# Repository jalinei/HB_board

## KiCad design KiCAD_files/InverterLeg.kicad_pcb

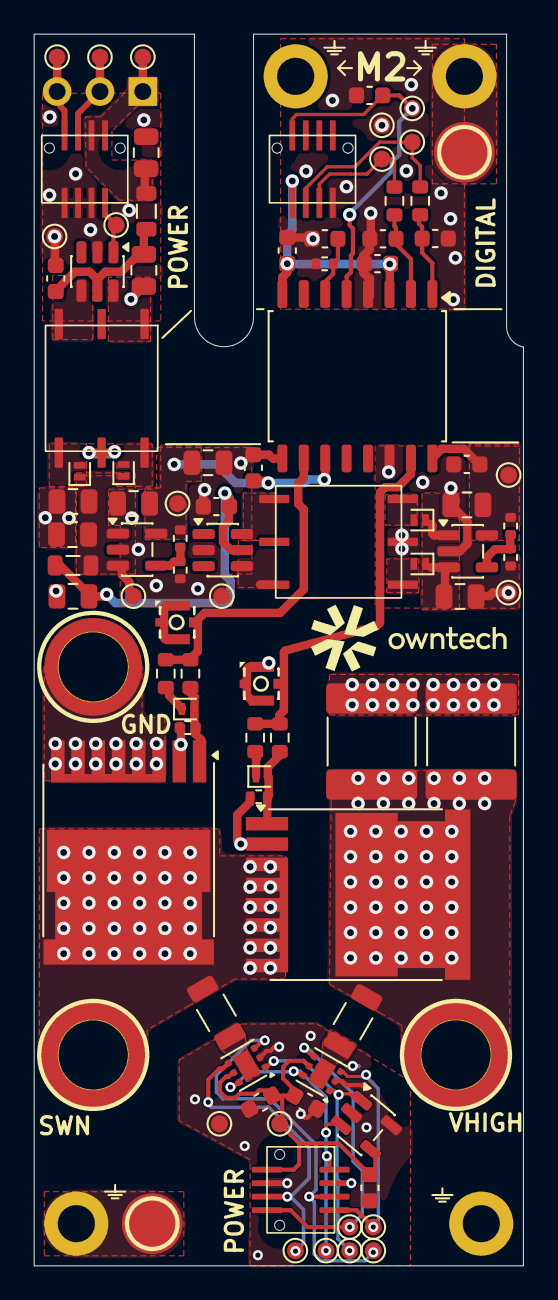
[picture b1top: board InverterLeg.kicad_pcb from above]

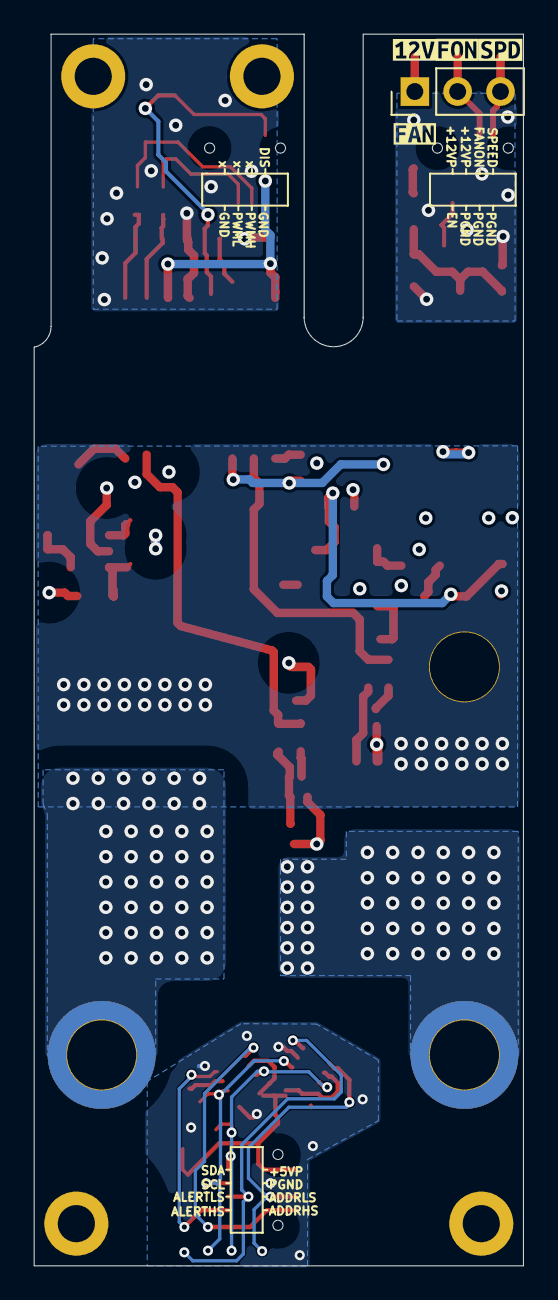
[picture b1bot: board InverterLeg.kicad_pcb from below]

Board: 4 copper layers, 29.0 x 73.0 mm, 100 parts (5 on the bottom side), 52 nets.

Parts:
C602, C605, C612, C614, C713, C733, C751, C754, C755: 100nF; C_0603_1608Metric
C604, C703: 20pF; C_0603_1608Metric
C607, C608: 1nF; C_0603_1608Metric
C616, C709, C711, C717, C718, C719, C731, C732, C734: 10uF; C_0805_2012Metric
C624, C626: 3.3uF; C_2220_5750Metric
D601, D602, D703, D704, D709, D710: PMEG4010ESBYL; D_SOD-882
H801, H802, H803, H804: MountingHole_Pad; MountingHole_2.2mm_M2_DIN965_Pad
J801, J802: AIPEX-4; IPEX-SMD_4P-L1.7-W1.7-LS2.0-L-4
J803, J806: 2LC000-739; CONN-TH_2LC000-739
J804: Conn_01x03_Socket; PinHeader_1x03_P2.54mm_Vertical
J811, J814, J817: SMTSO3050CTJ; SMD-1_BD5.5-D4.0_H5
J825, J827, J831: HC-PBB08-2-08-M-H1.0-G1-R-P-04; HC-PBB02-2-08-Male
L703, L706: 10uH; L_0805_2012Metric
Q801, Q802: AGM15T05LL; Infineon_PG-HSOF-8-2
R601, R602, R603, R604: 1R; R_0603_1608Metric
R605, R606: 51R; R_0603_1608Metric
R607, R608, R611, R613: 10k; R_0402_1005Metric
R609: 20k; R_0402_1005Metric
R610, R612: 158k; R_0402_1005Metric
T801, T802: TE1212-1W6ENT; 12126CNT
TJ801, TJ804: THJP1206AST1; THJP_1206_3216Metric
TP801, TP802, TP803, TP804, TP805, TP806, TP807, TP808, TP809, TP810, TP811, TP812, TP813, TP814, TP815, TP816, TP817, TP818, TP819, TP820, TP821, TP822: TestPoint_Pad_D1.0mm_small_courtyard
U603: UCC21520DWR; SOIC-16W_7.5x10.3mm_P1.27mm
U704, U707: VPS8701B; SOT-23-6
U801, U802: SY6345AAC; TSOT-23-5
U803: 24C02S(XBLW); SOT-23-5
U811, U815: T117B; WSON-6-1EP_2x2mm_P0.65mm_EP1x1.6mm
kibuzzard-6A8EFC0A: G***; kibuzzard-6A8EFC0A
kibuzzard-6A8EFC24: G***; kibuzzard-6A8EFC24
kibuzzard-6A9553CF: G***; kibuzzard-6A9553CF
kibuzzard-6AA2AEDD: G***; kibuzzard-6AA2AEDD

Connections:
+5V_DGND: C602.1, C605.1, J831.5, U603.3 (VCCI), U603.8 (VCCI)
+5V_PGND: C751.1, C754.1, C755.2, J827.1, TP820.1 (1_1), U803.4 (VCC), U811.5 (V+), U815.5 (V+)
+12V_PGND: C709.1, J804.1, J825.1, J825.2, L703.1, TP807.1 (1_1)
/12V_{HSRAW}: C734.1, D709.1 (K), D710.1 (K), U801.1 (VIN), U801.3 (~SHDN)
/12V_{HS}: C612.1, C719.1, R610.2, TP810.1 (1_1), U603.16 (VDDA), U801.5 (VOUT)
/12V_{LSRAW}: C717.1, C731.1, D703.1 (K), D704.1 (K), L706.1, TP814.1 (1_1), U802.1 (VIN), U802.3 (~SHDN)
/12V_{LS}: C614.1, C616.1, C718.1, R612.2, TP812.1 (1_1), U603.11 (VDDB), U802.5 (VOUT)
/ADDR_HS: J827.4, TP822.1 (1_1), U815.4 (ADD0)
/ADDR_LS: J827.3, TP821.1 (1_1), U811.4 (ADD0)
/ALERT_HS: J827.5, TP818.1 (1_1), U815.3 (ALERT)
/ALERT_LS: J827.6, TP817.1 (1_1), U811.3 (ALERT)
/DIS: C608.1, J831.4, TP803.1 (1_1), U603.5 (DIS)
/EN: J825.8, TP805.1 (1_1), U704.1 (EN)
/FAN_{ON}: J804.2, J825.3, TP808.1 (1_1)
/GND_{LS}: C624.2, C626.2, J814.1 (Pin_1_1), Q801.3 (S)
/K_{GNDLS}: C614.2, C616.2, C717.2, C718.2, C731.2, C732.2, C733.2, J802.2 (Ext), J802.3 (Ext), J802.4 (Ext), Q801.2 (DS), R608.1, R613.1, T802.5, TP813.1 (1_1), U603.9 (VSSB), U707.2 (GND), U802.2 (GND)
/K_{SWN}: C612.2, C719.2, C734.2, J801.2 (Ext), J801.3 (Ext), J801.4 (Ext), Q802.2 (DS), R607.1, R611.1, T801.5, TP811.1 (1_1), U603.14 (VSSA), U801.2 (GND)
/PWMH_{MCU}: J831.6, R605.1, TP801.1 (1_1)
/PWML_{MCU}: J831.7, R606.1, TP802.1 (1_1)
/PWM_{HS}: J801.1 (In), R601.1, R602.1, U603.15 (OUTA)
/PWM_{LS}: J802.1 (In), R603.1, R604.1, U603.10 (OUTB)
/SCL_{PWR}: J827.7, TP816.1 (1_1), U803.1 (SCL), U811.1 (SCL), U815.1 (SCL)
/SDA_{PWR}: J827.8, TP815.1 (1_1), U803.3 (SDA), U811.6 (SDA), U815.6 (SDA)
/SPEED: J804.3, J825.4, TP809.1 (1_1)
/SWN: J817.1 (Pin_1_1), Q801.4 (D), Q802.3 (S), TJ804.1 (Pin1)
/V_{IHigh_PGND}: C624.1, C626.1, J811.1 (Pin_1_1), Q802.4 (D), TJ801.1 (Pin1)
DGND: C602.2, C604.2, C605.2, C607.2, C608.2, C703.2, J831.8, R609.1, TP804.1 (1_1), U603.4 (GND)
Earth_Protective2: H802.1 (1_1), J806.1 (Pin_1_1)
Earth_Protective3: H803.1 (1_1), J803.1 (Pin_1_1)
unnamed: D601.2 (A), Q801.1 (G), R604.2, R608.2
unnamed: D601.1 (K), R603.2
unnamed: D602.2 (A), Q802.1 (G), R602.2, R607.2
unnamed: D602.1 (K), R601.2
unnamed: D703.2 (A), T802.6
unnamed: D704.2 (A), T802.4
unnamed: D709.2 (A), T801.6
unnamed: D710.2 (A), T801.4
unnamed: TJ801.2 (Pin2), U815.7 (TPad)
unnamed: TJ804.2 (Pin2), U811.7 (TPad)
unnamed: C607.1, R609.2, U603.6 (DT)
unnamed: C703.1, R605.2, U603.1 (INA)
unnamed: C604.1, R606.2, U603.2 (INB)
unnamed: T802.1, U704.6 (VD1)
unnamed: T802.3, U704.4 (VD2)
unnamed: C711.1, C713.1, L703.2, U704.5 (VIN)
unnamed: T801.1, U707.6 (VD1)
unnamed: T801.3, U707.4 (VD2)
unnamed: C732.1, C733.1, L706.2, U707.5 (VIN)
unnamed: R610.1, R611.2, U801.4 (ADJ)
unnamed: R612.1, R613.2, U802.4 (ADJ)
PGND: C751.2, C754.2, C755.1, J827.2, TP819.1 (1_1), U803.2 (GND), U803.5 (WP), U811.2 (GND), U815.2 (GND)
PGND2: C709.2, C711.2, C713.2, J825.5, J825.6, J825.7, TP806.1 (1_1), U704.2 (GND)

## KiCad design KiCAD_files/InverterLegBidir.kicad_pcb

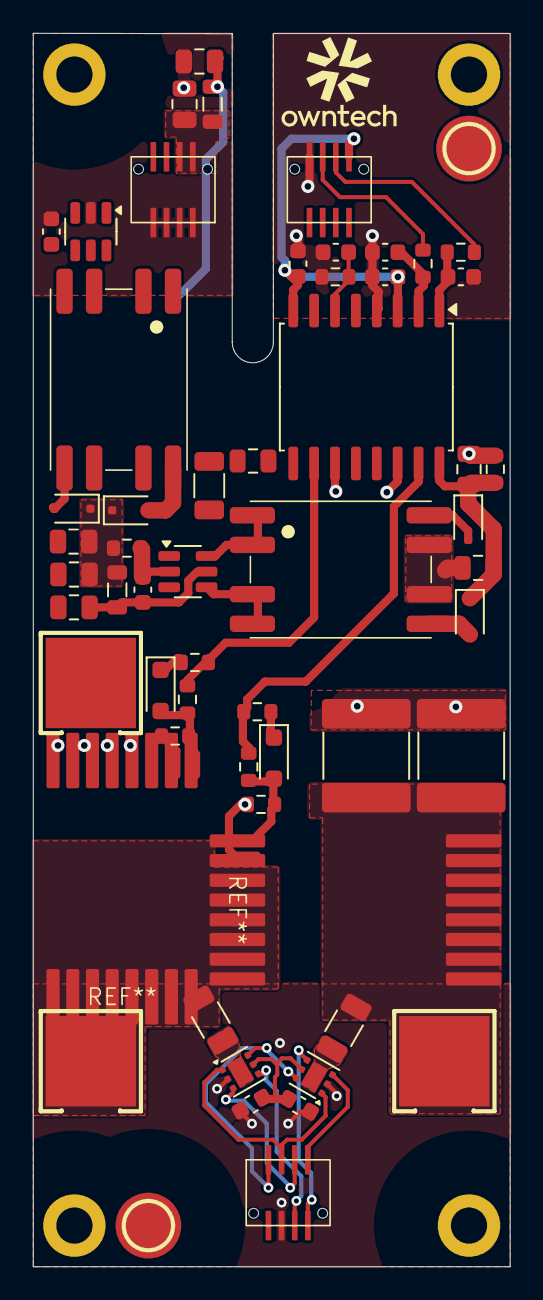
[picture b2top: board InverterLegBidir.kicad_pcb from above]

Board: 4 copper layers, 29.0 x 75.0 mm, 60 parts (0 on the bottom side), 42 nets.

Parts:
C602, C605, C607, C713, C733, C751, C754: 100nF; C_0603_1608Metric
C604, C703: 20pF; C_0603_1608Metric
C612, C614: 100nF; C_0805_2012Metric
C616: 10uF; C_1206_3216Metric
C624, C626: 4.7uF; C_2220_5750Metric
C709, C711, C717, C731, C732, C734: 10uF; C_0805_2012Metric
D601, D602: PMEG3010CEJ,115; D_SOD-323_HandSoldering
D703, D704, D709, D710: PMEG3010; D_SOD-323F
H801, H802, H803, H804: MountingHole_Pad; MountingHole_2.2mm_M2_DIN965_Pad
J803, J806: Conn_01x01_Pin; CONN-TH_2LC000-739
J811, J814, J817: Screw_Terminal_01x01; SMD_L5.0-W5.0_CON1_5X5_SMD
J825, J827, J831: Conn_02x02_Top_Bottom; HC-PBB02-2-08-M
L703, L706: 10uH; L_0805_2012Metric
R601, R603: 0R; R_0603_1608Metric
R602, R604: 2.2R; R_0603_1608Metric
R605, R606: 51R; R_0603_1608Metric
R607, R608: 1k; R_0603_1608Metric
R609: 20k; R_0603_1608Metric
R710, R713: 4.7k; R_0603_1608Metric
TJ801, TJ804: Thermal_Jumper; R_1206_3216Metric
TR701, TR704: VPT87DDF01B; VPT87BB-01B
U603: UCC21222DR; SOIC-16W_7.5x10.3mm_P1.27mm
U704, U707: VPS8701B; SOT-23-6
U811, U815: TMP117xxDRV; WSON-6-1EP_2x2mm_P0.65mm_EP1x1.6mm

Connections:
/5V_{DGND}: C602.1, C605.1, J831.1, U603.3 (VCCI), U603.8 (VCCI)
/5V_{PGND}: C751.1, C754.1, U811.5 (V+), U815.5 (V+)
/12V_{HS}: C612.1, C734.1, D709.1 (K), D710.1 (K), R713.1, U603.16 (VDDA)
/12V_{LS}: C614.1, C616.1, C717.1, C731.1, D703.1 (K), D704.1 (K), L706.1, R710.1, U603.11 (VDDB)
/12V_{PGND}: C709.1, J825.1, J825.2, J825.3, L703.1
/ADDR_HS: J827.4, U815.4 (ADD0)
/ADDR_LS: J827.3, U811.4 (ADD0)
/ALERT_HS: J827.5, U815.3 (ALERT)
/ALERT_LS: J827.6, U811.3 (ALERT)
/EN: J825.4, U704.1 (EN)
/GND_{LS}: C614.2, C616.2, C624.2, C626.2, C717.2, C731.2, C732.2, C733.2, J814.1 (Pin_1_1), R710.2, TR701.6 (SB), TR701.7 (SA), U603.9 (VSSB), U707.2 (GND)
/K_{SWN}: C612.2, C734.2, R607.1, R713.2, TR704.6 (SB), TR704.7 (SA), U603.14 (VSSA)
/PGND: C709.2, C711.2, C713.2, C751.2, C754.2, J825.5, J825.6, J825.7, J825.8, J827.2, U704.2 (GND), U811.2 (GND), U815.2 (GND)
/PWMH_{MCU}: J831.2, R605.1
/PWML_{MCU}: J831.3, R606.1
/PWM_{HS}: R601.1, R602.1, U603.15 (OUTA)
/PWM_{LS}: R603.1, R604.1, U603.10 (OUTB)
/SCL_{PWR}: J827.7, U811.1 (SCL), U815.1 (SCL)
/SDA_{PWR}: J827.8, U811.6 (SDA), U815.6 (SDA)
/SWN: J817.1 (Pin_1_1), TJ804.1 (Pin1)
/V_{IHigh_PGND}: C624.1, C626.1, J811.1 (Pin_1_1), TJ801.1 (Pin1)
DGND: C602.2, C604.2, C605.2, C607.2, C703.2, J831.4, R609.1, U603.4 (GND)
Earth_Protective: H801.1 (1_1), H802.1 (1_1), H803.1 (1_1), H804.1 (1_1), J803.1 (Pin_1_1), J806.1 (Pin_1_1)
unnamed: D601.2 (A), R604.2, R608.2
unnamed: D601.1 (K), R603.2
unnamed: D602.2 (A), R602.2, R607.2
unnamed: D602.1 (K), R601.2
unnamed: D703.2 (A), TR701.8 (SB)
unnamed: D704.2 (A), TR701.5 (SA)
unnamed: D709.2 (A), TR704.8 (SB)
unnamed: D710.2 (A), TR704.5 (SA)
unnamed: TJ801.2 (Pin2), U815.7 (TPad)
unnamed: TJ804.2 (Pin2), U811.7 (TPad)
unnamed: C607.1, R609.2, U603.6 (DT)
unnamed: C703.1, R605.2, U603.1 (INA)
unnamed: C604.1, R606.2, U603.2 (INB)
unnamed: TR701.1 (AA), TR701.2 (AA), U704.6 (VD1)
unnamed: TR701.3 (AB), TR701.4 (AB), U704.4 (VD2)
unnamed: C711.1, C713.1, L703.2, U704.5 (VIN)
unnamed: TR704.1 (AA), TR704.2 (AA), U707.6 (VD1)
unnamed: TR704.3 (AB), TR704.4 (AB), U707.4 (VD2)
unnamed: C732.1, C733.1, L706.2, U707.5 (VIN)
